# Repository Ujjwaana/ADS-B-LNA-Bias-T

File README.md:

# ADS-B-LNA-Bias-T
Bias-T Powered LNA For ADS-B Reception

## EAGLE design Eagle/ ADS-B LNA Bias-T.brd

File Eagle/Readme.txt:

EDA Files in Autodesk Eagle 9.xx format

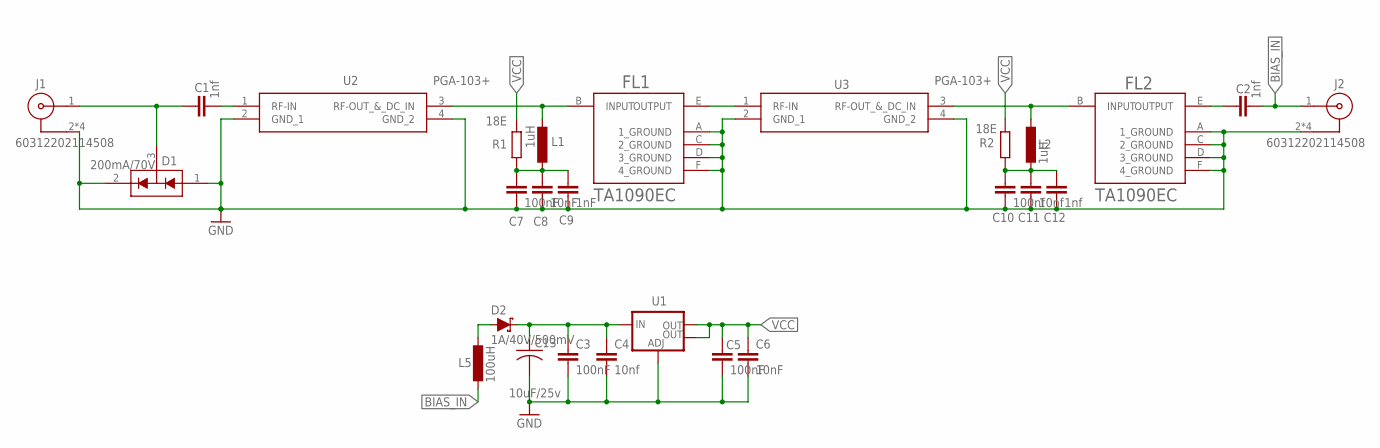
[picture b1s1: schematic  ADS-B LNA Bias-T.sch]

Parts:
C1, C2, C12: 1nf; C0603K
C3, C5, C7: 100nF; C0603K
C4, C11: 10nf; C0603K
C6, C8: 10nF; C0603K
C9: 1nF; C0603K
C10: 100nf; C0603K
C13: 10uF/25v; C3216
D1: 200mA/70V; SOT23-3
D2: 1A/40V/500mV; SMA-DIODE
FL1, FL2: TAI-SAW_TECHNOLOGY_TA1090ECTAI-SAW_TECHNOLOGY_TA1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; TAI-SAW_TECHNOLOGY_TA1090EC_0
J1, J2: 60312202114508
L1: 1uH; L3230M
L2: 1uH; L3225M
L5: 100uH; L4532M
R1, R2: 18E; R1206
U1: V_REG_LM1117SOT223; SOT223
U2, U3: PGA-103+; GVA63

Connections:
BIAS_IN: C2.2, J2.1, L5.2
GND: C3.2, C4.2, C5.2, C6.2, C7.2, C8.2, C9.2, C10.2, C11.2, C12.2, C13.2, D1.1 (A1), D1.2 (C2), FL1.A (1_GROUND), FL1.C (2_GROUND), FL1.D (3_GROUND), FL1.F (4_GROUND), FL2.A (1_GROUND), FL2.C (2_GROUND), FL2.D (3_GROUND), FL2.F (4_GROUND), J1.2, J1.3 (2), J1.4 (2), J1.5 (2), J2.2, J2.3 (2), J2.4 (2), J2.5 (2), U1.1 (ADJ), U2.2 (GND_1), U2.4 (GND_2), U3.2 (GND_1), U3.4 (GND_2)
unnamed: C1.2, U2.1 (RF-IN)
unnamed: C1.1, D1.3 (COM), J1.1
unnamed: FL1.E (OUTPUT), U3.1 (RF-IN)
unnamed: C7.1, C8.1, C9.1, L1.1, R1.2
unnamed: C2.1, FL2.E (OUTPUT)
unnamed: FL1.B (INPUT), L1.2, U2.3 (RF-OUT_&_DC_IN)
unnamed: C3.1, C4.1, C13.1, D2.C, U1.3 (IN)
unnamed: C10.1, C11.1, C12.1, L2.2, R2.2
unnamed: D2.A, L5.1
unnamed: FL2.B (INPUT), L2.1, U3.3 (RF-OUT_&_DC_IN)
VCC: C5.1, C6.1, R1.1, R2.1, U1.2 (OUT), U1.4 (OUT)

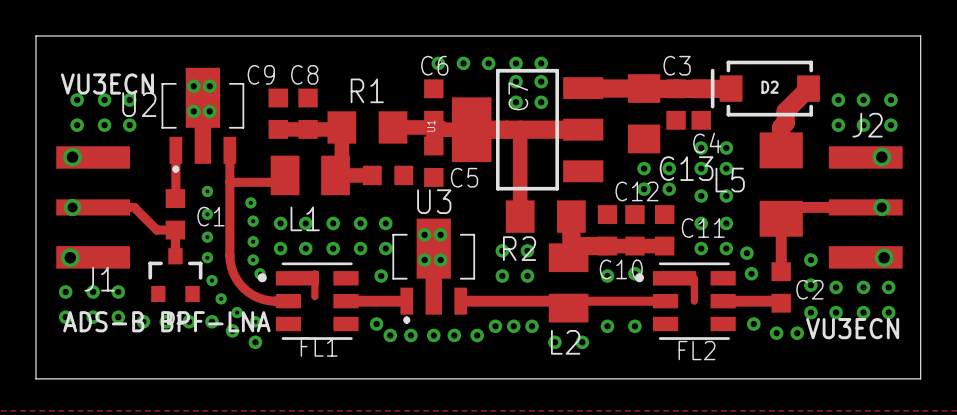
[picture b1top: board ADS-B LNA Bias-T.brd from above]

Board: 2 copper layers, 49.1 x 19.0 mm, 27 parts (0 on the bottom side), 13 nets.

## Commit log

2022-10-22 Adding the Eagle Files
2022-10-22 Adding the Gerber files
    Adding the Gerber files
2022-10-22 Adding Schematic PCB and Bom
    Adding Schematic PCB and Bom

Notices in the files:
parts and their libraries:
SparkFun-IC-Power: Licensing: Creative Commons ShareAlike 4.0 International - https://creativecommons.org/licenses/by-sa/4.0
